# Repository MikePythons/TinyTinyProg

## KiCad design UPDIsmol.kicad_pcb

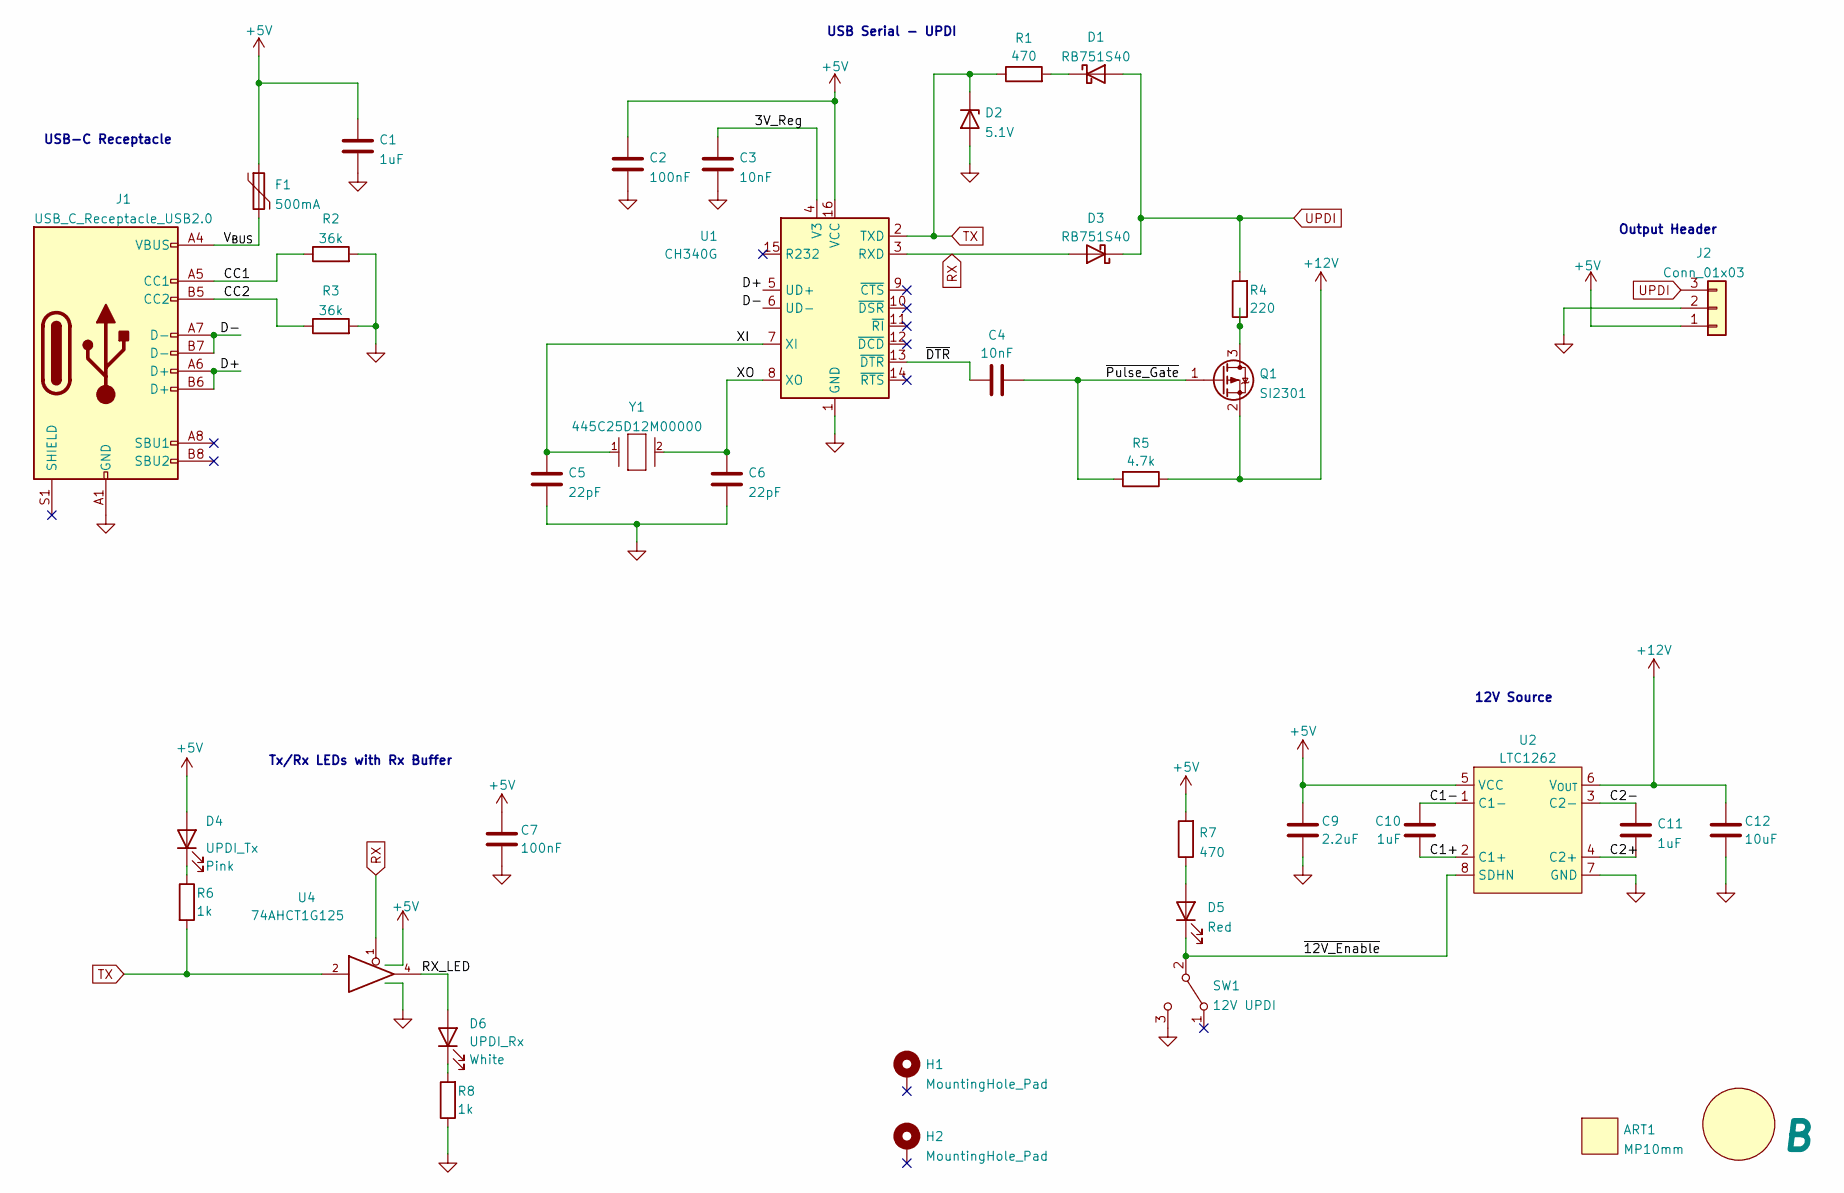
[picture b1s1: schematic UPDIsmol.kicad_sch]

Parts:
ART1: MP10mm; MPSquare_10mm
C1: 1uF; C_0603_1608Metric; Part CGA3E1X7R1C105K089AC
C2, C7: 100nF; C_0603_1608Metric
C3, C4: 10nF; C_0603_1608Metric
C5, C6: 22pF; C_0603_1608Metric
C9: 2.2uF; C_1206_3216Metric
C10, C11: 1uF; C_0805_2012Metric; Part 08055D105KAT2A
C12: 10uF; C_1206_3216Metric; Part GMK316BJ106ML-T
D1, D3: RB751S40; D_SOD-523
D2: 5.1V; D_MiniMELF
D4: UPDI_Tx; LED_0603_1608Metric
D5: Red; LED_0603_1608Metric
D6: UPDI_Rx; LED_0603_1608Metric
F1: 500mA; Fuse_1206_3216Metric_Pad1.42x1.75mm_HandSolder
H1, H2: MountingHole_Pad; MountingHole_2.2mm_M2_DIN965_Pad
J1: USB_C_Receptacle_USB2.0; USB_C_Receptacle_Palconn_UTC16-G
J2: Conn_01x03; PinHeader_1x03_P2.54mm_Horizontal
MISC1: B; RevisionSymbol
Q1: SI2301; SOT-23
R1, R7: 470; R_0603_1608Metric
R2, R3: 36k; R_0603_1608Metric
R4: 220; R_0603_1608Metric
R5: 4.7k; R_0603_1608Metric
R6, R8: 1k; R_0603_1608Metric
SW1: 12V UPDI; SW_SPDT_PCM12
U1: CH340G; SOIC-16_3.9x9.9mm_P1.27mm
U2: LTC1262; SOIC-8_3.9x4.9mm_P1.27mm
U4: 74AHCT1G125; SOT-553
Y1: 445C25D12M00000; Crystal-CTS-445-0-0-0; mouser part number 774-445C25D12M00000; digikey description CRYSTAL 12.0000MHZ 18PF SMD

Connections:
+5V: C1.2, C2.2, C7.2, C9.2, D4.2 (A), F1.1, J2.1, R7.2, U1.16 (VCC), U2.5 (VCC), U4.5 (5V)
+12V: C12.2, Q1.2 (S), R5.1, U2.6 (V_{OUT})
/3V_Reg: C3.2, U1.4 (V3)
/C1+: C10.1, U2.2 (C1+)
/C1-: C10.2, U2.1 (C1-)
/C2+: C11.1, U2.4 (C2+)
/C2-: C11.2, U2.3 (C2-)
/CC1: J1.A5 (CC1), R2.1
/CC2: J1.B5 (CC2), R3.1
/D+: J1.A6 (D+), J1.B6 (D+), U1.5 (UD+)
/D-: J1.A7 (D-), J1.B7 (D-), U1.6 (UD-)
/RX_LED: D6.2 (A), U4.4
/V_{BUS}: F1.2, J1.A4 (VBUS), J1.A9 (VBUS), J1.B4 (VBUS), J1.B9 (VBUS)
/XI: C5.2, U1.7 (XI), Y1.1
/XO: C6.2, U1.8 (XO), Y1.2
/~12V_Enable: D5.1 (K), SW1.2 (B), U2.8 (SDHN)
/~DTR: C4.1, U1.13 (~DTR)
/~Pulse_Gate: C4.2, Q1.1 (G), R5.2
GND: C1.1, C2.1, C3.1, C5.1, C6.1, C7.1, C9.1, C12.1, D2.2 (A), J1.A1 (GND), J1.A12 (GND), J1.B1 (GND), J1.B12 (GND), J2.2, R2.2, R3.2, R8.1, SW1.3 (C), U1.1 (GND), U2.7 (GND), U4.3 (GND)
unnamed: D1.1 (K), R1.2
unnamed: D4.1 (K), R6.1
unnamed: D5.2 (A), R7.1
unnamed: D6.1 (K), R8.2
unnamed: Q1.3 (D), R4.1
RX: D3.2 (A), U1.3 (RXD), U4.1
TX: D2.1 (K), R1.1, R6.2, U1.2 (TXD), U4.2
UPDI: D1.2 (A), D3.1 (K), J2.3, R4.2

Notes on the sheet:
Output Header
USB Serial - UPDI
USB-C Receptacle
12V Source
Tx/Rx LEDs with Rx Buffer

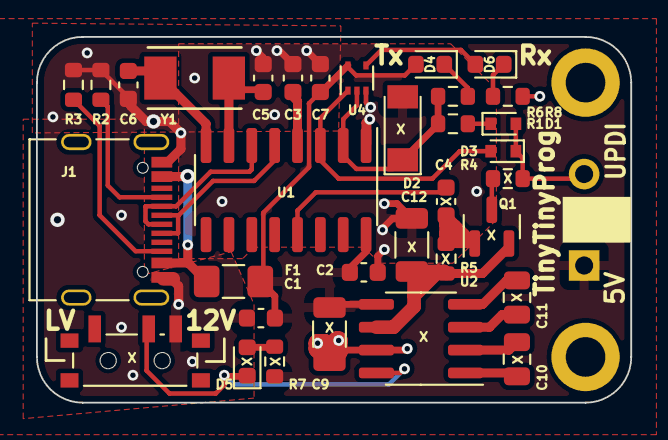
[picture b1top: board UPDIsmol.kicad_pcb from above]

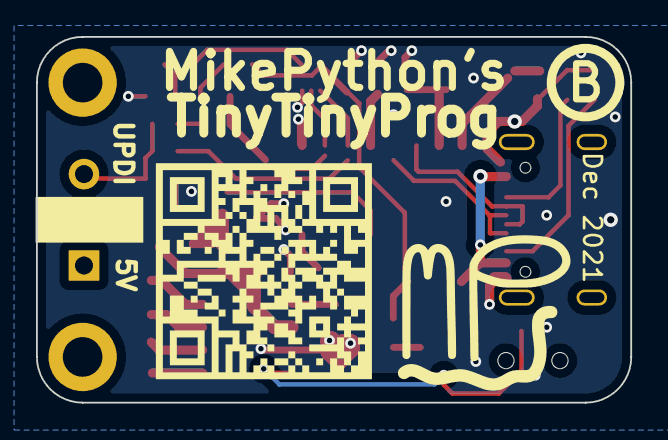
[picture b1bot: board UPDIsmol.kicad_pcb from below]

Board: 2 copper layers, 33.0 x 20.3 mm, 38 parts (3 on the bottom side), 27 nets.

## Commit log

2021-12-29 Revision B. Updated silkscreen + correct MOSFET footprint orientation.
2022-01-19 Tidied schematic, still RevB
